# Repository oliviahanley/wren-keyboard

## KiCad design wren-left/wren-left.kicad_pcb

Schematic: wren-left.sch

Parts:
D1, D2, D3, D4, D5, D6, D7, D8, D9, D10, D11, D12, D13, D14, D15, D16, D17, D18, D19, D20, D21, D22, D23, D24, D25, D26, D27, D28, D29, D30, D31, D32, D33, D34, D35, D36, D37, D38, D39, D40, D41, D42, D43, D44, D45: D_Small; D_SOD123_axial
ENC1: Rotary_Encoder_Switch; RotaryEncoder_Alps_EC11E-Switch_Vertical_H20mm
J1: TRRS_Jack; Jack_3.5mm_PJ320E_Horizontal
MX1, MX2, MX3, MX4, MX5, MX6, MX7, MX8, MX9, MX10, MX11, MX12, MX13, MX14, MX15, MX16, MX17, MX18, MX19, MX20, MX21, MX22, MX23, MX24, MX25, MX26, MX27, MX28, MX29, MX30, MX31, MX32, MX33, MX34, MX35, MX36, MX37, MX38, MX39, MX40, MX42, MX43, MX44: MX-NoLED; MX-1U
MX41: MX-NoLED; MX-2U-FLIPPED-ReversedStabilizers
R1: 2.2kOhms; R_Axial_DIN0204_L3.6mm_D1.6mm_P5.08mm_Vertical
R2: 10kOhms; R_Axial_DIN0204_L3.6mm_D1.6mm_P5.08mm_Vertical
SW0: Reset; SW_PUSH_6mm
U1: Elite-C

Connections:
COL0: ENC1.S1, MX1.1 (COL), MX11.1 (COL), MX21.1 (COL), MX31.1 (COL), U1.13 (10/PB6)
COL1: MX2.1 (COL), MX12.1 (COL), MX22.1 (COL), MX32.1 (COL), MX41.1 (COL), U1.14 (16/PB2)
COL2: MX3.1 (COL), MX13.1 (COL), MX23.1 (COL), MX33.1 (COL), MX42.1 (COL), U1.15 (14/PB3)
COL3: MX4.1 (COL), MX14.1 (COL), MX24.1 (COL), MX34.1 (COL), MX43.1 (COL), U1.16 (15/PB1)
COL4: MX5.1 (COL), MX15.1 (COL), MX25.1 (COL), MX35.1 (COL), MX44.1 (COL), U1.17 (A0/PF7)
COL5: MX6.1 (COL), MX16.1 (COL), MX26.1 (COL), MX36.1 (COL), U1.18 (A1/PF6)
COL6: MX7.1 (COL), MX17.1 (COL), MX27.1 (COL), MX37.1 (COL), U1.19 (A2/PF5)
COL7: MX8.1 (COL), MX18.1 (COL), MX28.1 (COL), MX38.1 (COL), U1.20 (A3/PF4)
COL8: MX9.1 (COL), MX19.1 (COL), MX29.1 (COL), MX39.1 (COL), U1.9 (6/PD7)
COL9: MX10.1 (COL), MX20.1 (COL), MX30.1 (COL), MX40.1 (COL), U1.10 (7/PE6)
ENC1-OUT: D41.2 (A), ENC1.S2
GND: ENC1.C, J1.T, SW0.2, U1.23 (GND)
LEFT: ENC1.A, U1.29 (F0)
unnamed: D1.2 (A), MX1.2 (ROW)
unnamed: D2.2 (A), MX2.2 (ROW)
unnamed: D3.2 (A), MX3.2 (ROW)
unnamed: D4.2 (A), MX4.2 (ROW)
unnamed: D5.2 (A), MX5.2 (ROW)
unnamed: D6.2 (A), MX6.2 (ROW)
unnamed: D7.2 (A), MX7.2 (ROW)
unnamed: D8.2 (A), MX8.2 (ROW)
unnamed: D9.2 (A), MX9.2 (ROW)
unnamed: D10.2 (A), MX10.2 (ROW)
unnamed: D11.2 (A), MX11.2 (ROW)
unnamed: D12.2 (A), MX12.2 (ROW)
unnamed: D13.2 (A), MX13.2 (ROW)
unnamed: D14.2 (A), MX14.2 (ROW)
unnamed: D15.2 (A), MX15.2 (ROW)
unnamed: D16.2 (A), MX16.2 (ROW)
unnamed: D17.2 (A), MX17.2 (ROW)
unnamed: D18.2 (A), MX18.2 (ROW)
unnamed: D19.2 (A), MX19.2 (ROW)
unnamed: D20.2 (A), MX20.2 (ROW)
unnamed: D21.2 (A), MX21.2 (ROW)
unnamed: D22.2 (A), MX22.2 (ROW)
unnamed: D23.2 (A), MX23.2 (ROW)
unnamed: D24.2 (A), MX24.2 (ROW)
unnamed: D25.2 (A), MX25.2 (ROW)
unnamed: D26.2 (A), MX26.2 (ROW)
unnamed: D27.2 (A), MX27.2 (ROW)
unnamed: D28.2 (A), MX28.2 (ROW)
unnamed: D29.2 (A), MX29.2 (ROW)
unnamed: D30.2 (A), MX30.2 (ROW)
unnamed: D31.2 (A), MX31.2 (ROW)
unnamed: D32.2 (A), MX32.2 (ROW)
unnamed: D33.2 (A), MX33.2 (ROW)
unnamed: D34.2 (A), MX34.2 (ROW)
unnamed: D35.2 (A), MX35.2 (ROW)
unnamed: D36.2 (A), MX36.2 (ROW)
unnamed: D37.2 (A), MX37.2 (ROW)
unnamed: D38.2 (A), MX38.2 (ROW)
unnamed: D39.2 (A), MX39.2 (ROW)
unnamed: D40.2 (A), MX40.2 (ROW)
unnamed: D42.2 (A), MX41.2 (ROW)
unnamed: D43.2 (A), MX42.2 (ROW)
unnamed: D44.2 (A), MX43.2 (ROW)
unnamed: D45.2 (A), MX44.2 (ROW)
unnamed: SW0.1, U1.22 (RST)
RIGHT: ENC1.B, U1.28 (F1)
ROW0: D1.1 (K), D2.1 (K), D3.1 (K), D4.1 (K), D5.1 (K), D6.1 (K), D7.1 (K), D8.1 (K), D9.1 (K), D10.1 (K), U1.1 (TX0/PD3)
ROW1: D11.1 (K), D12.1 (K), D13.1 (K), D14.1 (K), D15.1 (K), D16.1 (K), D17.1 (K), D18.1 (K), D19.1 (K), D20.1 (K), U1.2 (RX1/PD2)
ROW2: D21.1 (K), D22.1 (K), D23.1 (K), D24.1 (K), D25.1 (K), D26.1 (K), D27.1 (K), D28.1 (K), D29.1 (K), D30.1 (K), U1.7 (4/PD4)
ROW3: D31.1 (K), D32.1 (K), D33.1 (K), D34.1 (K), D35.1 (K), D36.1 (K), D37.1 (K), D38.1 (K), D39.1 (K), D40.1 (K), U1.8 (5/PC6)
ROW4: D41.1 (K), D42.1 (K), D43.1 (K), D44.1 (K), D45.1 (K), U1.12 (9/PB5)
SCL: J1.R2, R2.1, U1.6 (3/PD0)
SDA: J1.S, R1.1, U1.5 (2/PD1)
VCC: J1.R1, R1.2, R2.2, U1.21 (VCC)

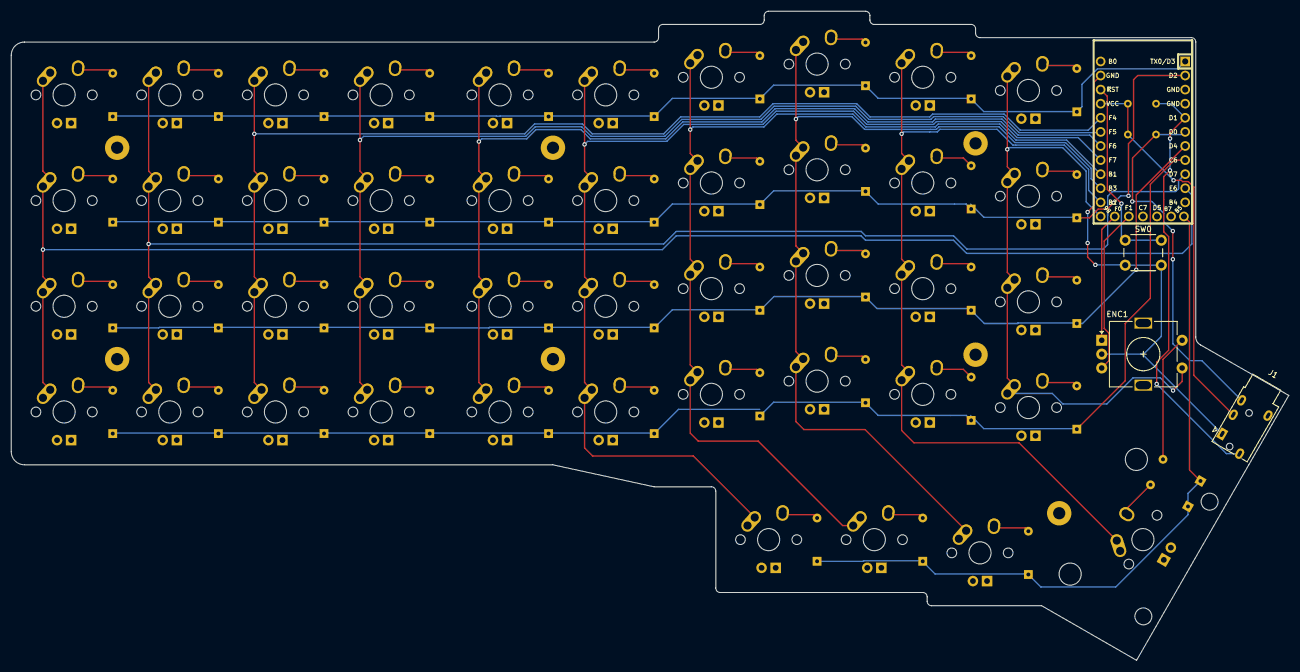
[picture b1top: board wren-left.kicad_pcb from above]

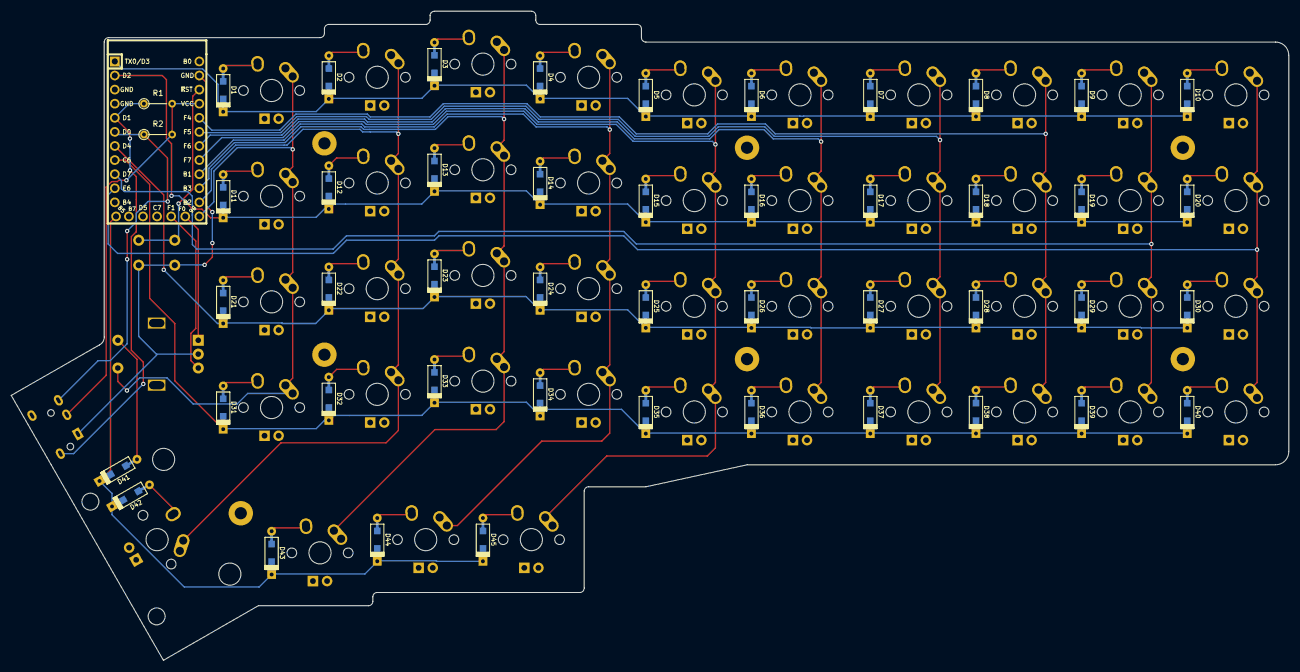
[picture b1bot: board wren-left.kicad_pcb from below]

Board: 2 copper layers, 230.3 x 117.0 mm, 95 parts (48 on the bottom side), 67 nets.
